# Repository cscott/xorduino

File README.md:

This is an Open Hardware peripheral for the OLPC XO-1/1.5/1.75/4.

The files are created using Eagle 6.2.0 on Linux and the SparkFun footprint
libraries.

Strong inspiration drawn from the following Open Hardware designs (thanks for
sharing!):
* The Arduino Leonardo (arduino-compatible ATmega32U4 design)
* SparkFun's ATmega32U4 breakout <http://www.sparkfun.com/products/11117>
  for figuring out which parts of the Leonardo design are actually
  mandatory
* SparkFun's Scratch Sensor Board-compatible PicoBoard
    <http://www.sparkfun.com/products/10311>

Some notes:

0. This board integrates Arduino, Scratch Sensor Board, and turtle robot
   functionality.  There are many optional parts: if you want to build
   just the Arduino, you may; if you want to populate the robot functionality
   but not the sensor board, that's fine, too.  If you populate the
   peripherals but not the ATmega32u4 processor, this makes a splendid
   "shield" for the XO Stick -- one way to amortize the cost of
   the robot functionality is to have just one XOrduino-bot shield per
   classroom, while still giving the kids their own XO Stick "brains"
   which they can mount on top of it.

    The "bot" features of the board include a current-limited motor driver,
   two bump switches at the front of the board, and two optical sensors
   for measuring motor rotation, allowing the user to write code like
   "rotate left 90 degrees" instead of "rotate left 2 seconds", which
   experimentally kids find much harder to understand.  The XOrduino
   board mounts on a Tamiya Twin Motor Gearbox (part #70097), and there's
   a mounting hole for a ~25mm long standoff to serve as a front skid.

    The motors are set up to draw 1A max, which matches the power source
   ability of the XO's USB ports.  The USB standard only allows 500mA
   draw, which would require adjusting F1 and RN7.

1. Many of the Leonardo design's components are optional in a
   lowest-possible-cost design, for a number of different reasons:
   a) USB port protection which is already included on the XO
      motherboard,
   b) ESD and protection diodes (helpful but not required),
   c) bypass caps and ferrites for less noise on analog signals
      (helpful but not required).
   Wherever possible I've included the pads anyway, so that less
   budget-conscious users can populate these components.  At times
   this has required jumper traces which you need to cut if you
   decide to populate the optional components.

2. I eliminated the multi-way 3.3V/5V internal/external power supply
   functionality of the Arduino to save cost.  The XOrduino is 5V
   only, powered by the USB port.  The Arduino "3.3V" pin on the
   shield connector is left disconnected.  I've replaced this with
   a lower cost step-up regulator, allowing "bot" users to power
   the XOrduino with a 3-cell (4.5v) battery pack.  Again, all
   these components are optional: the XOrduino will run fine
   powered by its USB tether.

3. The first version of this board used a large number of through-hole
   parts.  This revision is less afraid of surface mount parts (since
   the ATmega32U4 is only available in an SMT package anyway), which
   save board space and lower BOM cost.  I'm attempting to make the
   XOrduino local-assembly-friendly, so I surface mount footprints are
   as large as possible: all discrete components are 0805 or larger.
   Like the XO Stick, this has been routed as a two layer board to
   lower reproduction costs, although if you fabricate with a 4-layer
   board you will get more robust power and ground planes.

    One possibly-controversial change in this version is to use
   surface mount resistor arrays to reduce part count and BOM cost;
   they may turn out to be too small to hand assemble.  We'll see.

4. I made this Scratch Sensor Board compatible.  Even though many of
   the scratch sensors are redudant on the XO (it has a microphone
   already, and the XO-1.75 includes an ambient light sensor), they
   gain new relevance in the "turtle bot" mode -- they make it easy to
   build a standalone robot which is "afraid of light", "stops when
   you clap", etc.  The scratch community has a large number of
   interesting examples based around the Scratch Sensor
   Board/Picoboard, many of which can use the 4 additional channels
   provided by the XOrduino ("color etch-a-sketch", for example, with
   knobs for X, Y, color, and line width).  I used 3.5mm jacks instead
   of the Picoboard-standard 2.5mm jacks in order to be compatible
   with probes built for the XO; I hope that was a good choice.

    See https://github.com/osbock/ScratchSensors for an arduino sketch
   to support the Scratch Sensor board functionality; it might be nicer
   to integrate this into the bootloader so that it's "always there".

5. There's a USB plug integrated with the PCB with break-off tabs to
   increase the thickness to the USB standard 1.6mm.  There are pads
   for a through-hole USB mini-B connector and a more-standard surface
   mount USB micro-B connector, but they are rather expensive (~$1).

    When the discrete connector is populated, it leaves the USB
   signals and power/gnd exposed on big metal tabs, which could be
   non-ideal.  Certainly you shouldn't plug in to more than one jack
   at a time.

  -- C. Scott Ananian, 2012-06-09, revised 2012-07-30, 2012-08-08.

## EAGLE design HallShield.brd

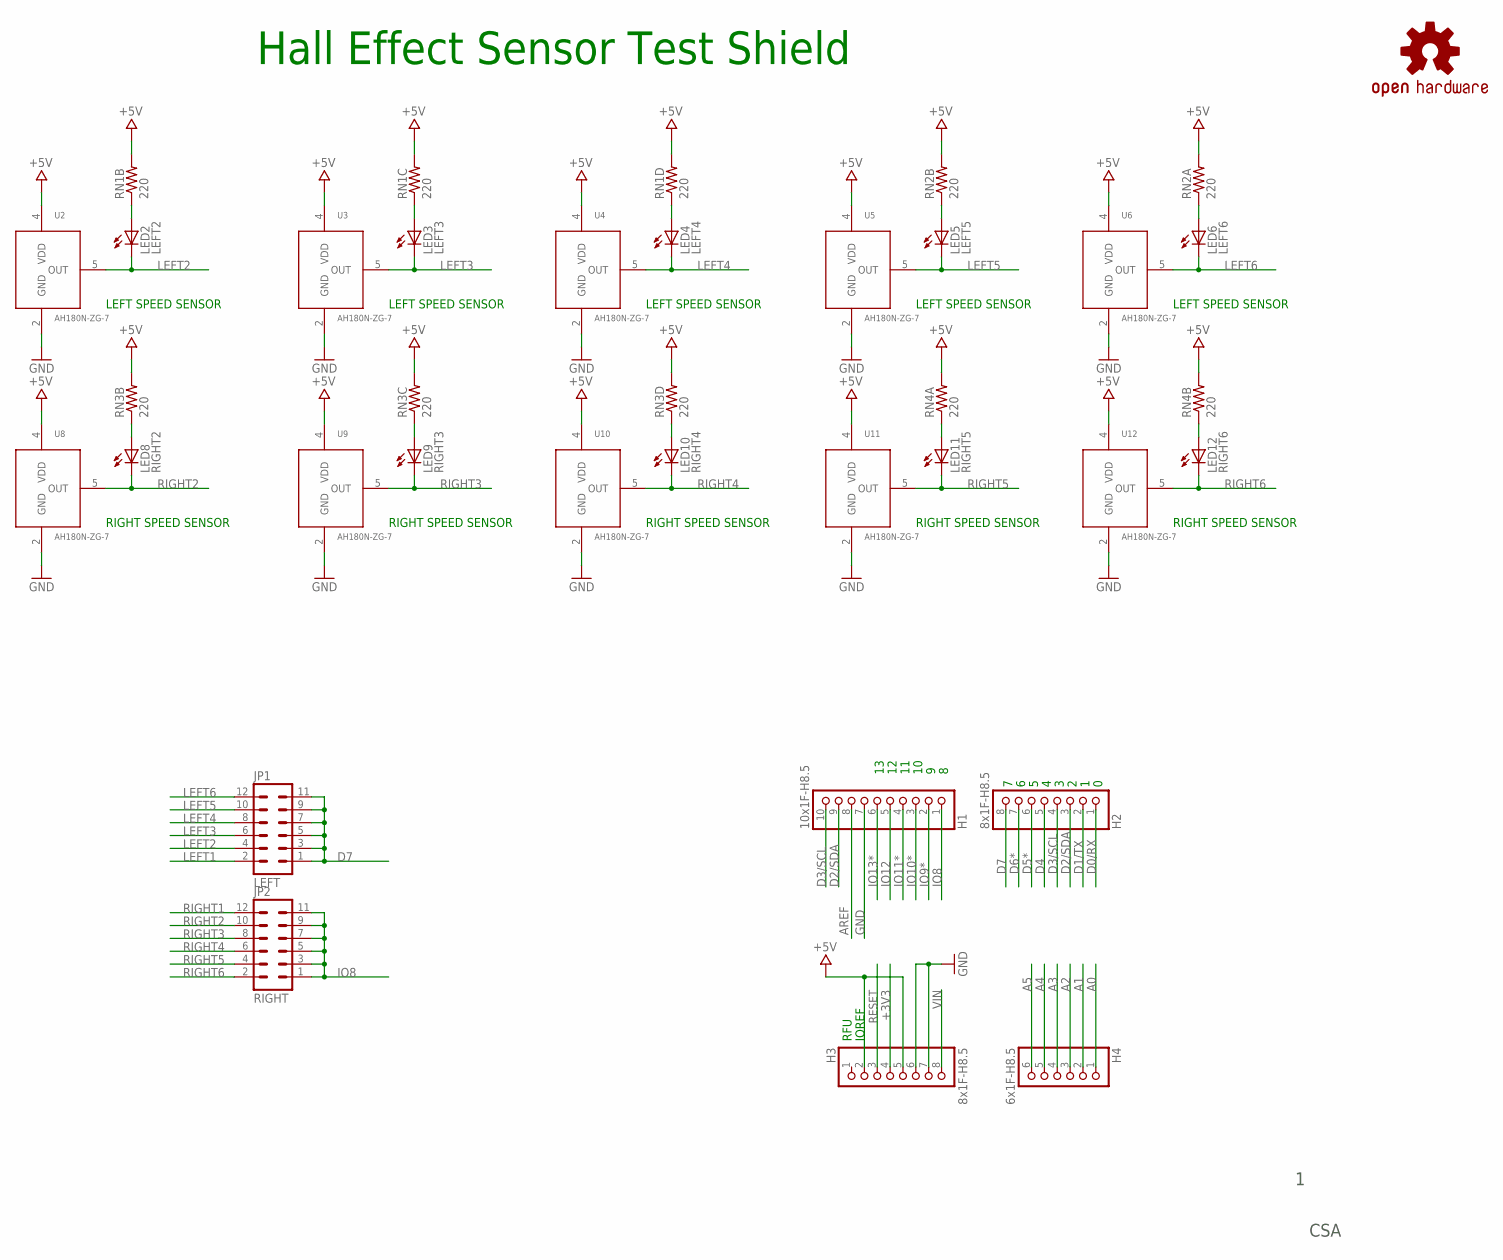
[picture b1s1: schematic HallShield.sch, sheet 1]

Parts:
H1: 10x1F-H8.5; 1X10
H2, H3: 8x1F-H8.5; 1X08
H4: 6x1F-H8.5; 1X06
JP1: LEFT; MA06-2
JP2: RIGHT; MA06-2
LED2: LEFT2; LED0805
LED3: LEFT3; LED0805
LED4: LEFT4; LED0805
LED5: LEFT5; LED0805
LED6: LEFT6; LED0805
LED8: RIGHT2; LED0805
LED9: RIGHT3; LED0805
LED10: RIGHT4; LED0805
LED11: RIGHT5; LED0805
LED12: RIGHT6; LED0805
RN1, RN2, RN3, RN4: 220; CRA06S
U2, U3, U4, U5, U6, U8, U9, U10, U11, U12: AH180N-ZG-7; SOT553
U$5: OSHW-LOGOL; OSHW-LOGO-L

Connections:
+3V3: H3.4
+5V: H3.2, H3.5, RN1.5 (2), RN1.6 (2), RN1.7 (2), RN2.7 (2), RN2.8 (2), RN3.5 (2), RN3.6 (2), RN3.7 (2), RN4.7 (2), RN4.8 (2), U2.4 (VDD), U3.4 (VDD), U4.4 (VDD), U5.4 (VDD), U6.4 (VDD), U8.4 (VDD), U9.4 (VDD), U10.4 (VDD), U11.4 (VDD), U12.4 (VDD); also elsewhere on the board
A0: H4.1
A1: H4.2
A2: H4.3
A3: H4.4
A4: H4.5
A5: H4.6
AREF: H1.8
D0/RX: H2.1
D1/TX: H2.2
D2/SDA: H1.9, H2.3
D3/SCL: H1.10, H2.4
D4: H2.5
D5*: H2.6
D6*: H2.7
D7: H2.8, JP1.1, JP1.3, JP1.5, JP1.7, JP1.9, JP1.11
GND: H1.7, H3.6, H3.7, U2.2 (GND), U3.2 (GND), U4.2 (GND), U5.2 (GND), U6.2 (GND), U8.2 (GND), U9.2 (GND), U10.2 (GND), U11.2 (GND), U12.2 (GND); also elsewhere on the board
IO8: H1.1, JP2.1, JP2.3, JP2.5, JP2.7, JP2.9, JP2.11
IO9*: H1.2
IO10*: H1.3
IO11*: H1.4
IO12: H1.5
IO13*: H1.6
LEFT1: JP1.2; also elsewhere on the board
LEFT2: JP1.4, LED2.C, U2.5 (OUT)
LEFT3: JP1.6, LED3.C, U3.5 (OUT)
LEFT4: JP1.8, LED4.C, U4.5 (OUT)
LEFT5: JP1.10, LED5.C, U5.5 (OUT)
LEFT6: JP1.12, LED6.C, U6.5 (OUT)
unnamed: LED2.A, RN1.2 (1)
unnamed: LED3.A, RN1.3 (1)
unnamed: LED4.A, RN1.4 (1)
unnamed: LED5.A, RN2.2 (1)
unnamed: LED6.A, RN2.1
unnamed: LED8.A, RN3.2 (1)
unnamed: LED9.A, RN3.3 (1)
unnamed: LED10.A, RN3.4 (1)
unnamed: LED11.A, RN4.1
unnamed: LED12.A, RN4.2 (1)
RESET: H3.3
RIGHT1: JP2.12; also elsewhere on the board
RIGHT2: JP2.10, LED8.C, U8.5 (OUT)
RIGHT3: JP2.8, LED9.C, U9.5 (OUT)
RIGHT4: JP2.6, LED10.C, U10.5 (OUT)
RIGHT5: JP2.4, LED11.C, U11.5 (OUT)
RIGHT6: JP2.2, LED12.C, U12.5 (OUT)
VIN: H3.8

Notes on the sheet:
Hall Effect Sensor Test Shield
IOREF
RFU
CSA
LEFT SPEED SENSOR
RIGHT SPEED SENSOR

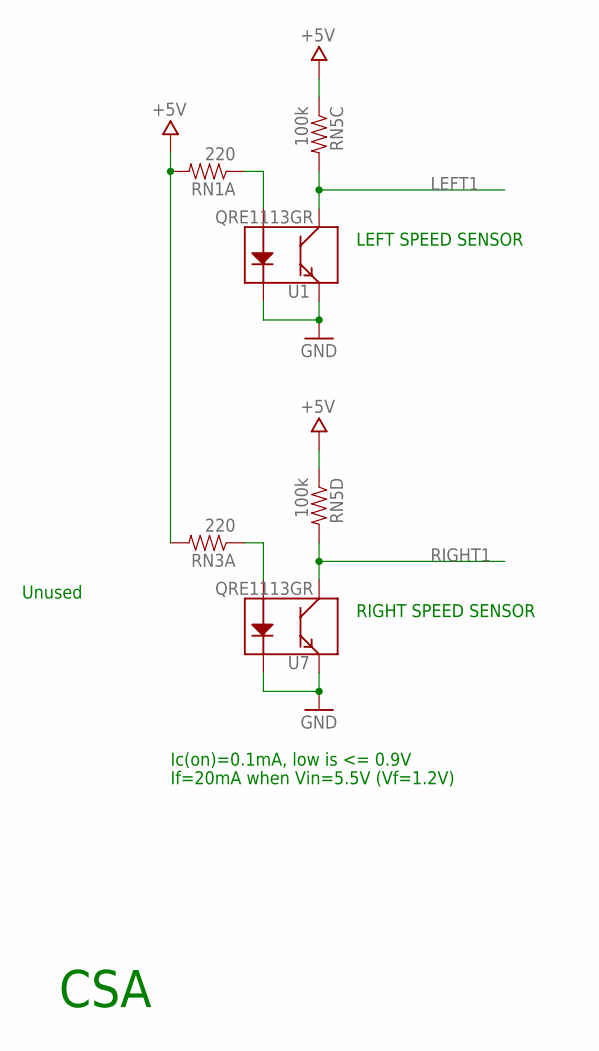
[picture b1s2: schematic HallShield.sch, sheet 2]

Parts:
RN1, RN3: 220; CRA06S
RN5: 100k; CRA06S
U1, U7: QRE1113GR

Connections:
+5V: RN1.8 (2), RN3.8 (2), RN5.3 (1), RN5.4 (1); also elsewhere on the board
GND: U1.2 (K), U1.4 (E), U7.2 (K), U7.4 (E); also elsewhere on the board
LEFT1: RN5.6 (2), U1.3 (C); also elsewhere on the board
RIGHT1: RN5.5 (2), U7.3 (C); also elsewhere on the board
U5_ANODE: RN1.1, U1.1 (A)
U6_ANODE: RN3.1, U7.1 (A)

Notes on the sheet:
LEFT SPEED SENSOR
RIGHT SPEED SENSOR
If=20mA when Vin=5.5V (Vf=1.2V)
Ic(on)=0.1mA, low is <= 0.9V
Unused
CSA

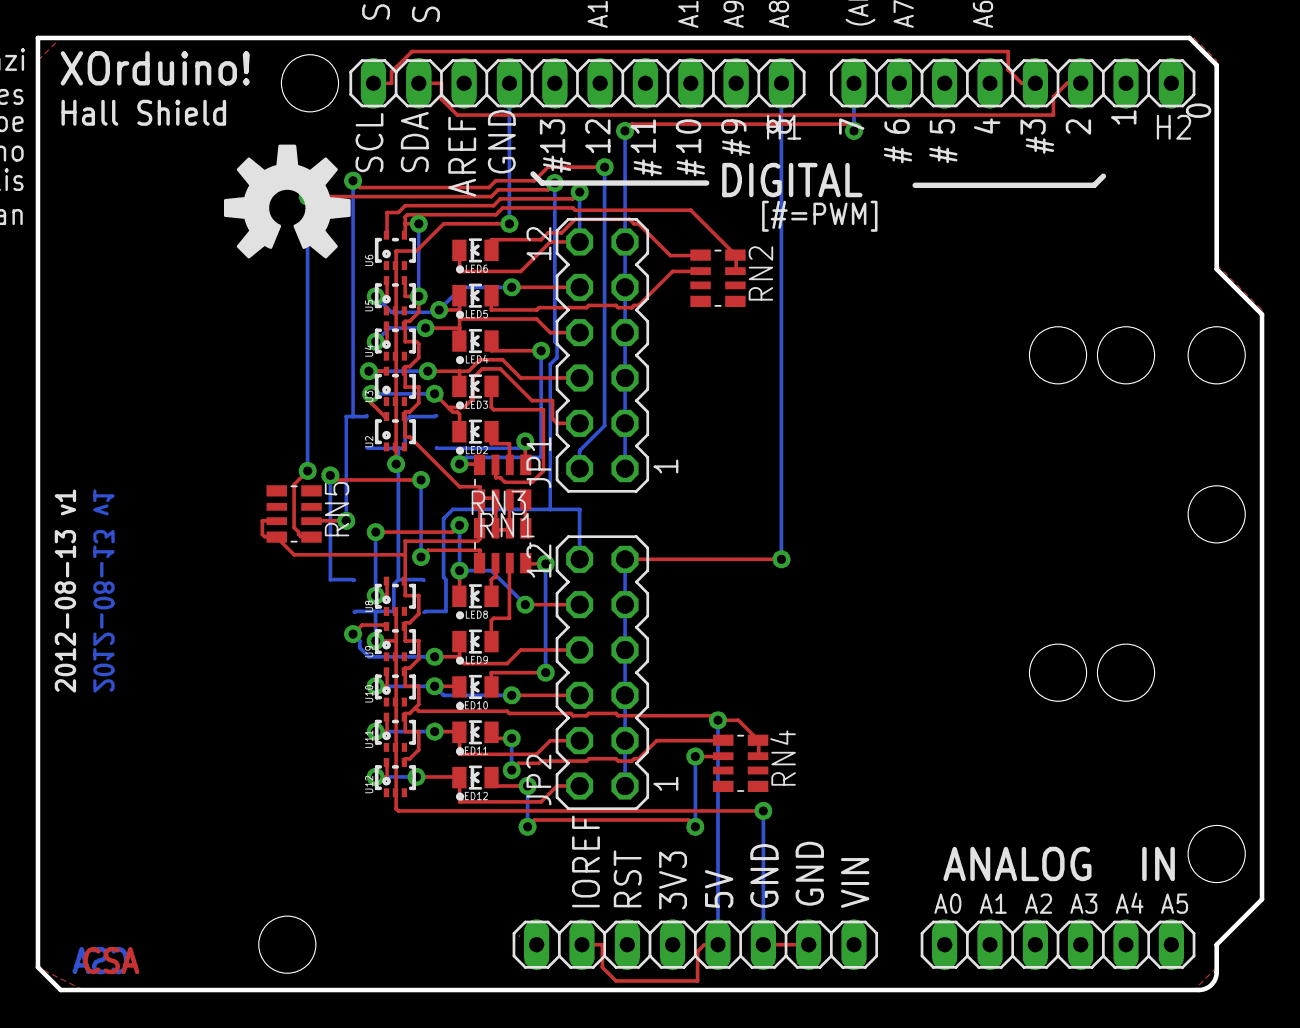
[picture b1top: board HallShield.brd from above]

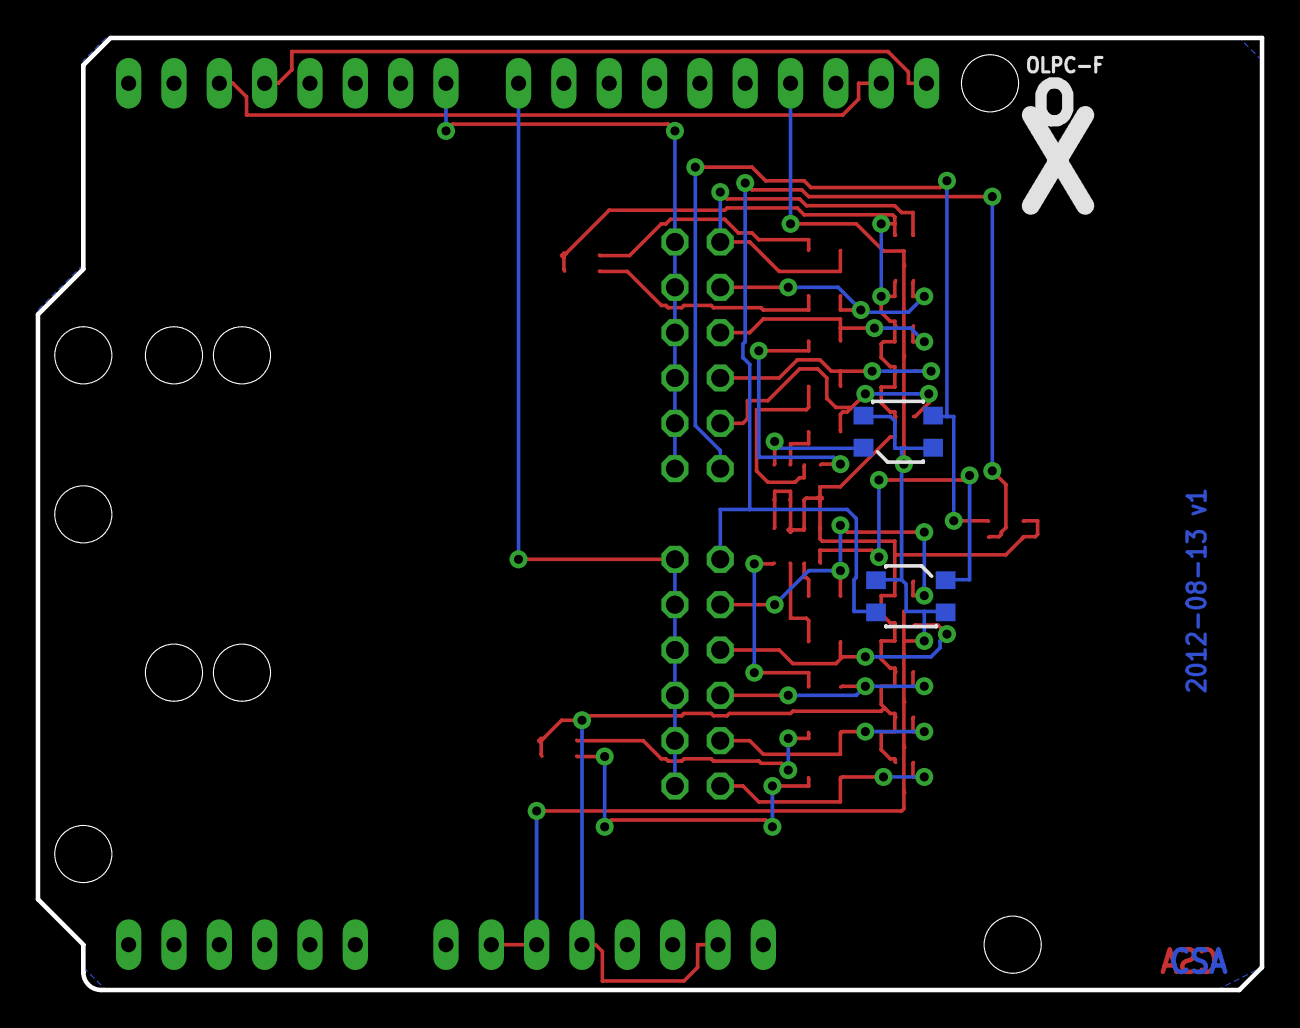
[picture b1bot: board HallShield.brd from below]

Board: 4 copper layers, 68.6 x 53.3 mm, 34 parts (2 on the bottom side), 30 nets.

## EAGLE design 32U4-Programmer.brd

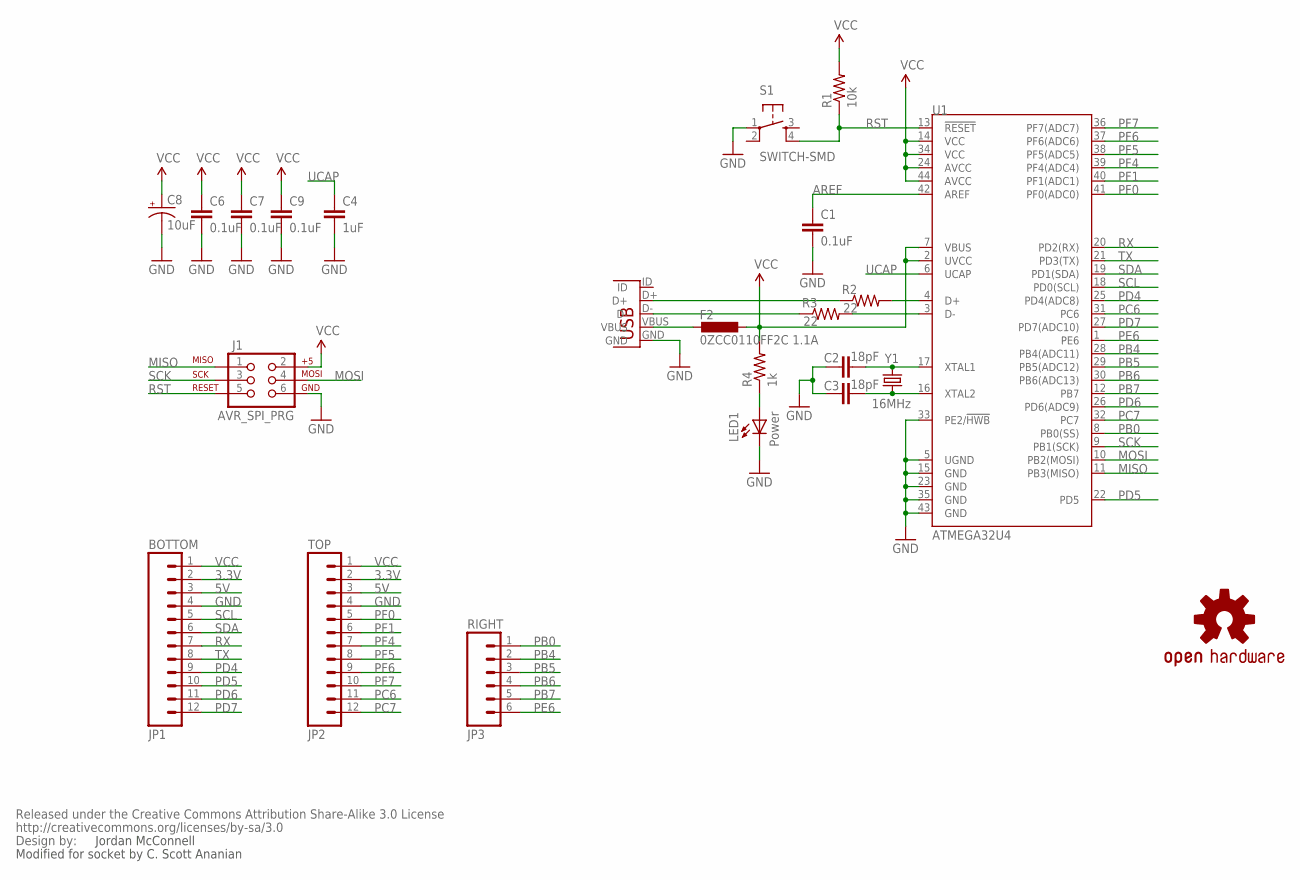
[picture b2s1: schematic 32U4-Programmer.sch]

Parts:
C1, C6, C7, C9: 0.1uF; CAP-PTH-SMALL
C2, C3: 18pF; CAP-PTH-SMALL
C4: 1uF; CAP-PTH-SMALL
C8: 10uF; CPOL-RADIAL-10UF-25V
F2: 0ZCC0110FF2C 1.1A; L1812
J1: AVR_SPI_PRG; 2X3
JP1: BOTTOM; 1X12
JP2: TOP; 1X12
JP3: RIGHT; 1X06
LED1: Power; LED3MM-KIT
R1: 10k; AXIAL-0.3
R2, R3: 22; AXIAL-0.3
R4: 1k; AXIAL-0.3
S1: SWITCH-SMD; TACTILE-PTH
U1: ATMEGA32U4; TQFP44-SOCKET
U$6: OSHW-LOGOM; OSHW-LOGO-M
U$7: CREATIVE_COMMONS
X1: USBMINIB; USB-MB-H2
Y1: 16MHz; HC49US

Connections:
3.3V: JP1.2, JP2.2
5V: JP1.3, JP2.3
AREF: C1.1, U1.42 (AREF)
D_M: R3.P$1 (1), X1.D-
D_P: R2.P$1 (1), X1.D+
GND: C1.2, C2.1, C3.1, C4.2, C6.2, C7.2, C8.2 (-), C9.2, J1.6, JP1.4, JP2.4, LED1.K (C), S1.1, U1.5 (UGND), U1.15 (GND), U1.23 (GND), U1.33 (PE2/!HWB), U1.35 (GND), U1.43 (GND), X1.GND
MISO: J1.1, U1.11 (PB3(MISO))
MOSI: J1.4, U1.10 (PB2(MOSI))
unnamed: F2.2, X1.VBUS
unnamed: C2.2, U1.17 (XTAL1), Y1.2
unnamed: C3.2, U1.16 (XTAL2), Y1.1
unnamed: LED1.A, R4.P$1 (1)
PB0: JP3.1, U1.8 (PB0(SS))
PB4: JP3.2, U1.28 (PB4(ADC11))
PB5: JP3.3, U1.29 (PB5(ADC12))
PB6: JP3.4, U1.30 (PB6(ADC13))
PB7: JP3.5, U1.12 (PB7)
PC6: JP2.11, U1.31 (PC6)
PC7: JP2.12, U1.32 (PC7)
PD4: JP1.9, U1.25 (PD4(ADC8))
PD5: JP1.10, U1.22 (PD5)
PD6: JP1.11, U1.26 (PD6(ADC9))
PD7: JP1.12, U1.27 (PD7(ADC10))
PE6: JP3.6, U1.1 (PE6)
PF0: JP2.5, U1.41 (PF0(ADC0))
PF1: JP2.6, U1.40 (PF1(ADC1))
PF4: JP2.7, U1.39 (PF4(ADC4))
PF5: JP2.8, U1.38 (PF5(ADC5))
PF6: JP2.9, U1.37 (PF6(ADC6))
PF7: JP2.10, U1.36 (PF7(ADC7))
RD_M: R3.P$2 (2), U1.3 (D-)
RD_P: R2.P$2 (2), U1.4 (D+)
RST: J1.5, R1.P$1 (1), S1.4, U1.13 (!RESET)
RX: JP1.7, U1.20 (PD2(RX))
SCK: J1.3, U1.9 (PB1(SCK))
SCL: JP1.5, U1.18 (PD0(SCL))
SDA: JP1.6, U1.19 (PD1(SDA))
TX: JP1.8, U1.21 (PD3(TX))
UCAP: C4.1, U1.6 (UCAP)
VCC: C6.1, C7.1, C8.1 (+), C9.1, F2.1, J1.2, JP1.1, JP2.1, R1.P$2 (2), R4.P$2 (2), U1.2 (UVCC), U1.7 (VBUS), U1.14 (VCC), U1.24 (AVCC), U1.34 (VCC), U1.44 (AVCC)

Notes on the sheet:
Jordan McConnell
Modified for socket by C. Scott Ananian

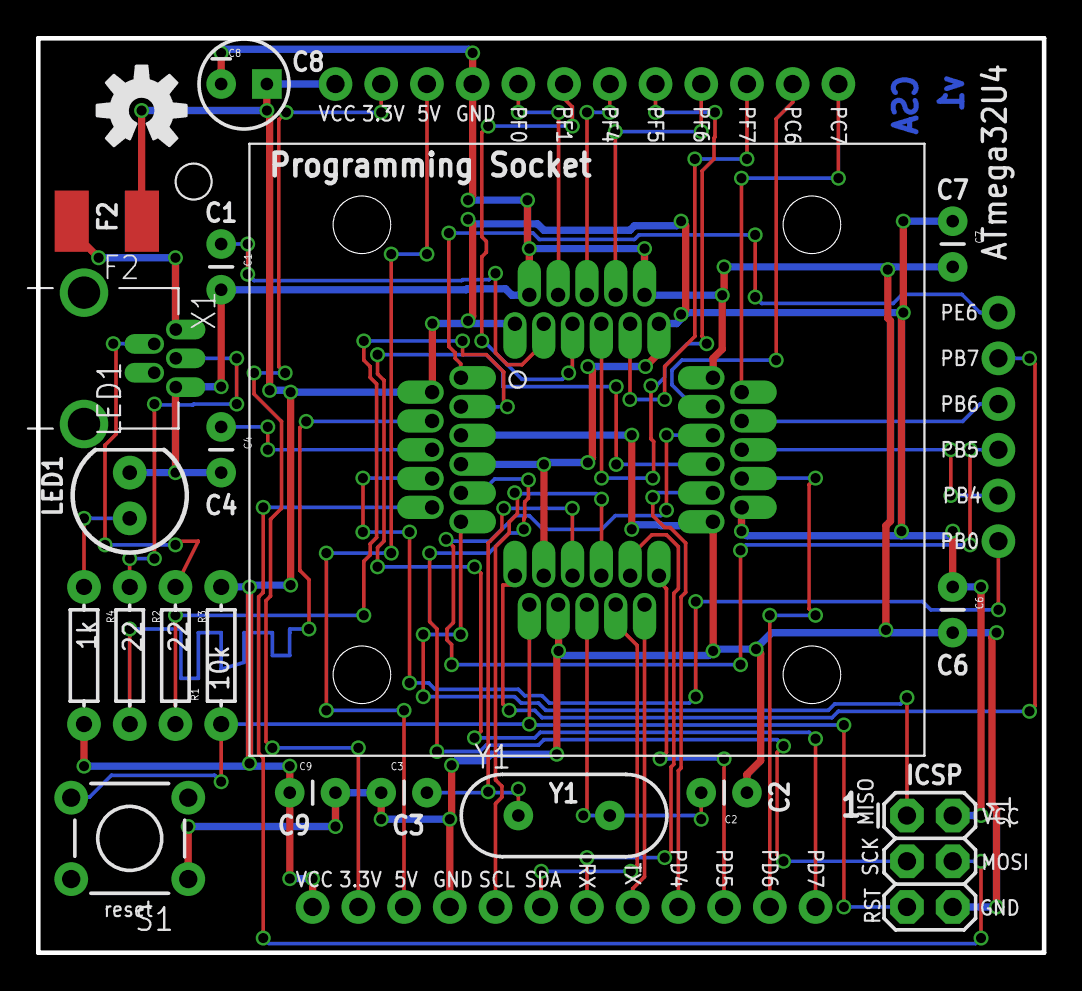
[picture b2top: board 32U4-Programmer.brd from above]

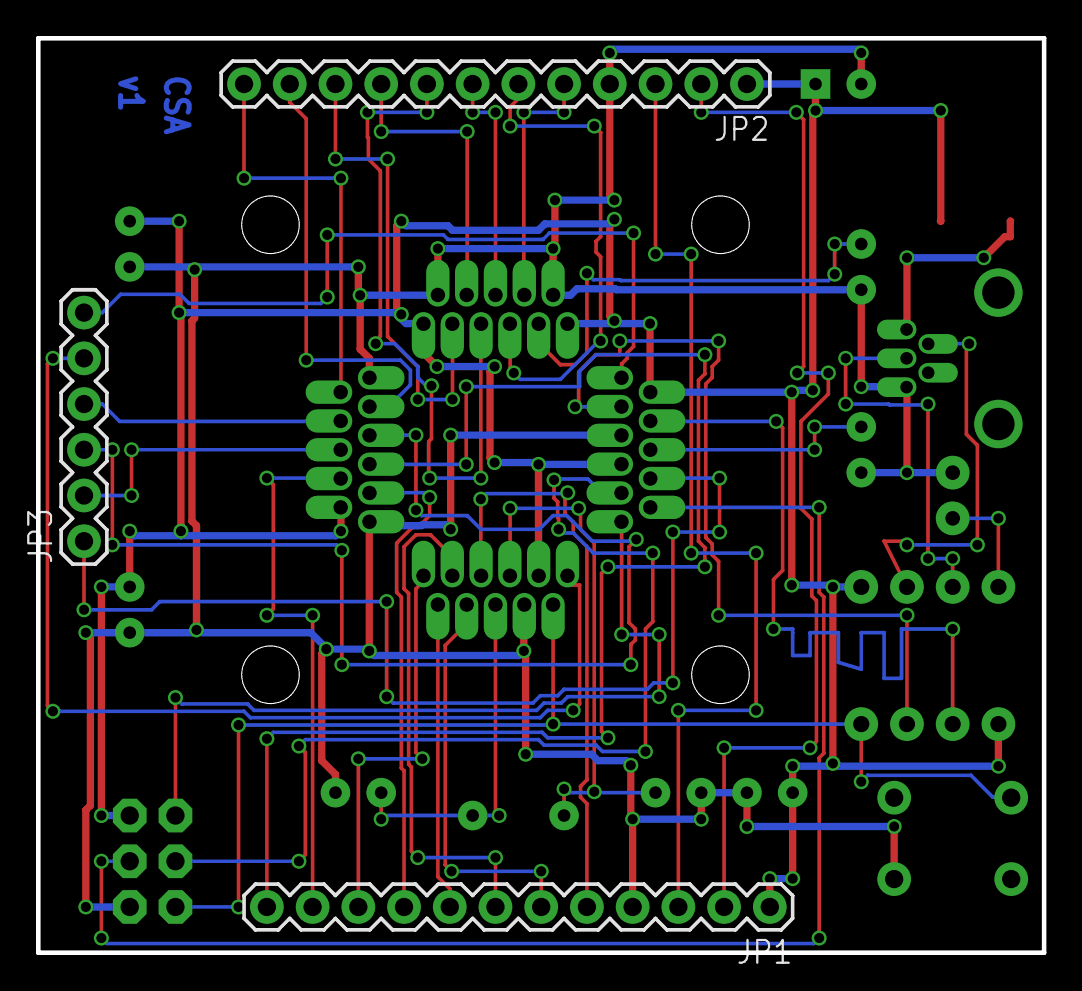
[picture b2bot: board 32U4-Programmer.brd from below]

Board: 2 copper layers, 55.9 x 50.8 mm, 24 parts (3 on the bottom side), 40 nets.

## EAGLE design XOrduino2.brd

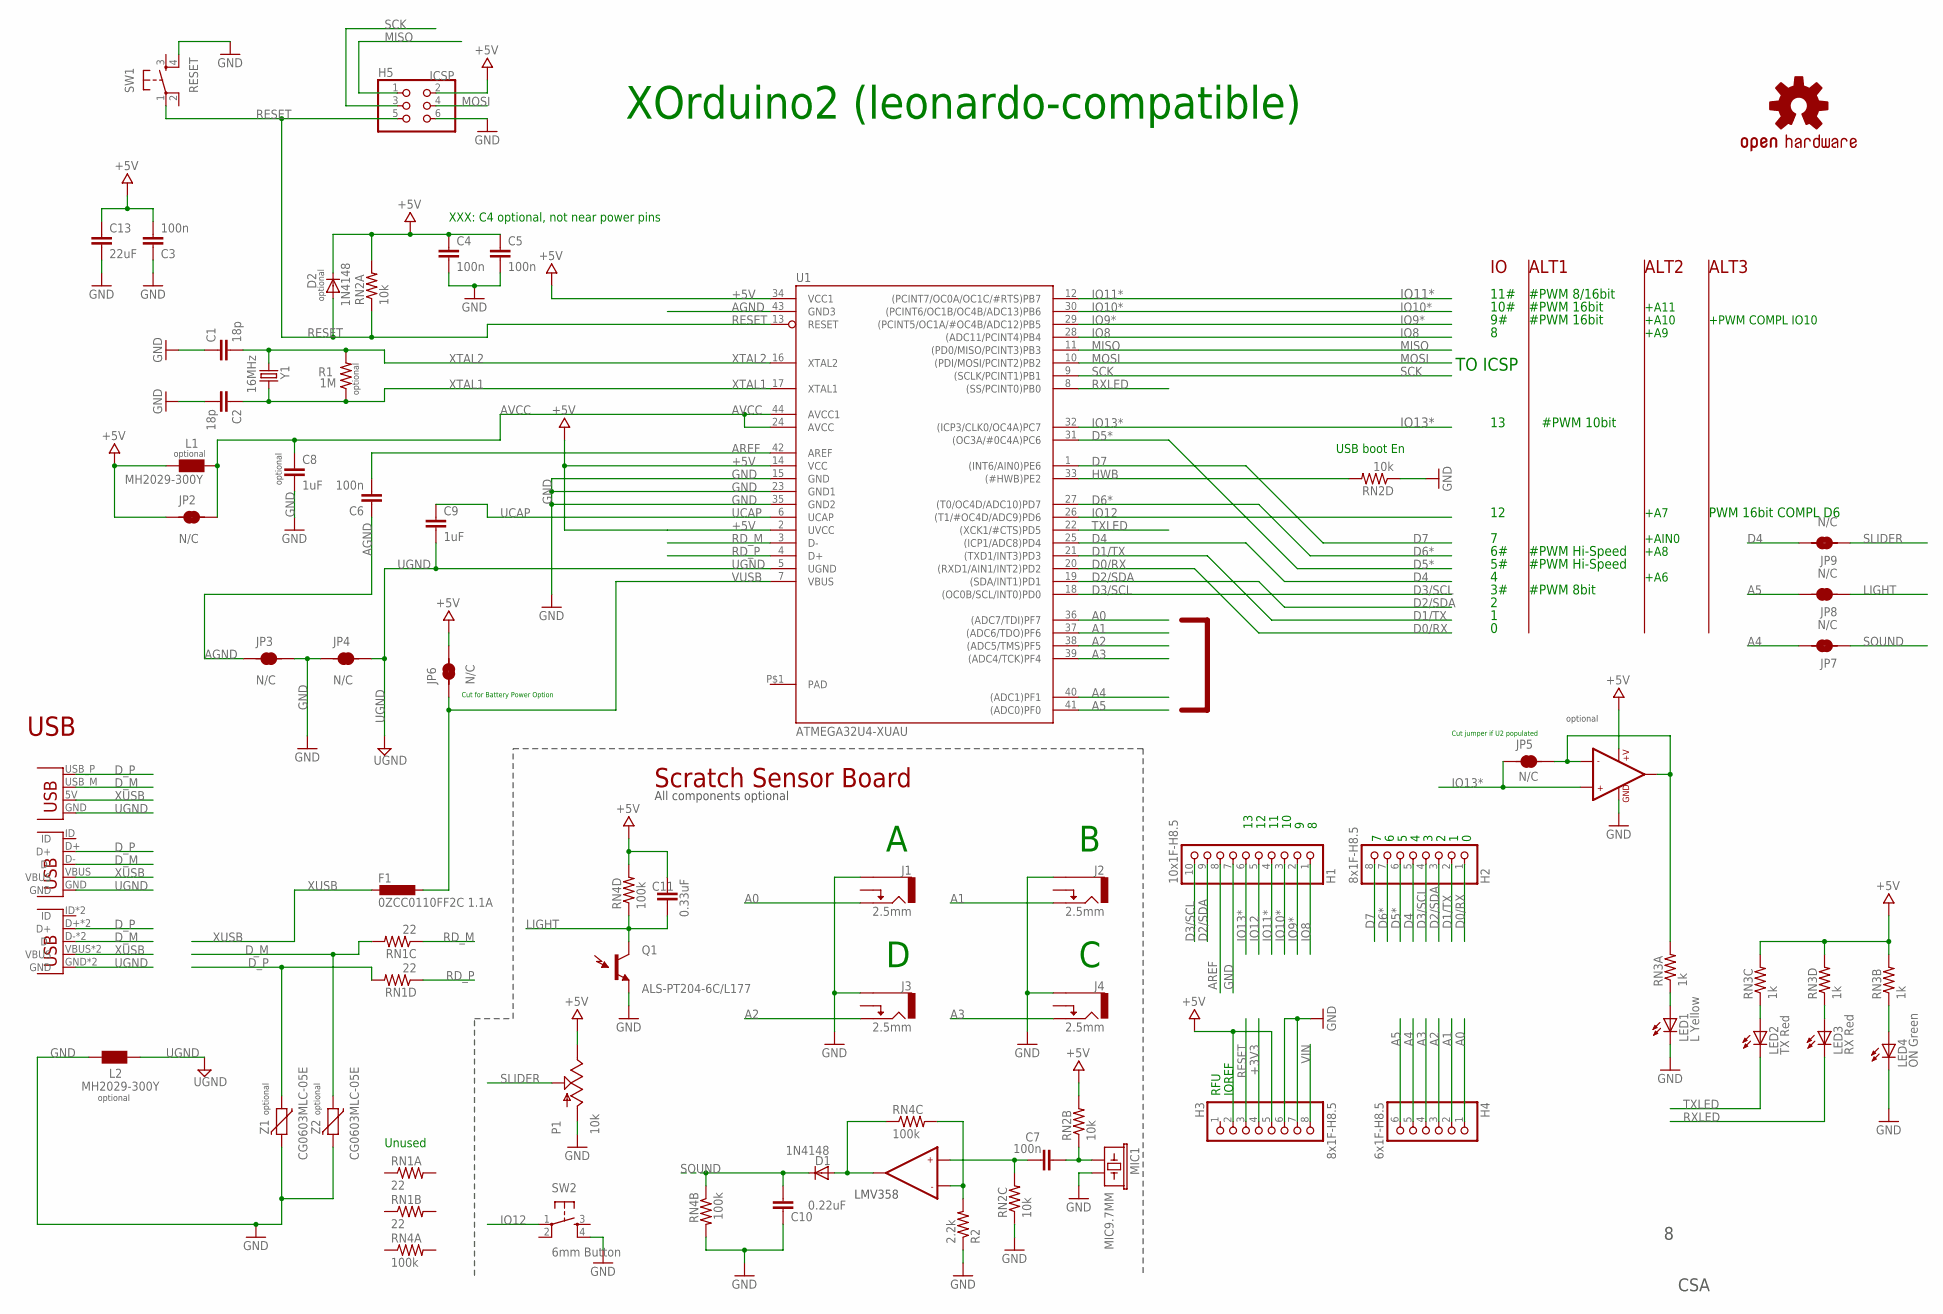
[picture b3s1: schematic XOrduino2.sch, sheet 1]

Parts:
C1, C2: 18p; 0805
C3, C4, C5, C6, C7: 100n; 0805
C8, C9: 1uF; 0805
C10: 0.22uF; 0805
C11: 0.33uF; 0805
C13: 22uF; 1206
D1, D2: 1N4148; DIODE-1N4148
F1: 0ZCC0110FF2C 1.1A; L1812
H1: 10x1F-H8.5; 1X10
H2, H3: 8x1F-H8.5; 1X08
H4: 6x1F-H8.5; 1X06
H5: ICSP; 2X03
J1, J2, J3, J4: 2.5mm; MJ-3523-SMT
JP2, JP3, JP4, JP5, JP6: N/C; SJ-2S-TRACE-NOCONFLICT
JP7, JP8: N/C; SJ-2S-BOT-TRACE-VIA-NOCONFLICT
JP9: N/C; SJ-2S-BOT-TRACE-NOCONFLICT
L1, L2: MH2029-300Y; 0805
LED1: L Yellow; LED0805
LED2: TX Red; LED0805
LED3: RX Red; LED0805
LED4: ON Green; LED0805
MIC1: MIC9.7MM; MIC-9.7MM
P1: 10k; P091N
Q1: ALS-PT204-6C/L177; LED3MM-KIT
R1: 1M; 0805
R2: 2.2k; 0805
RN1: 22; CRA06S
RN2: 10k; CRA06S
RN3: 1k; CRA06S
RN4: 100k; CRA06S
SW1: RESET; TACTILE-PTH
SW2: 6mm Button; TACTILE-PTH
U1: ATMEGA32U4-XUAU; TQFP44-PAD
U2: LMV358; SO08
U$5: OSHW-LOGOL; OSHW-LOGO-L
X1: USBPCB; USB-A-PCB
X2: USBMINIB; USB-MB-H2
X3: USBMICROB-VIA; USB-MICROB-VIA
Y1: 16MHz; HC49US
Z1, Z2: CG0603MLC-05E; CT/CN0603

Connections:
+3V3: H3.4
+5V: C3.2, C4.1, C5.1, C11.1, C13.1, D2.C, H3.2, H3.5, H5.2, JP2.1, JP6.2, L1.1, P1.1 (E), RN2.7 (2), RN2.8 (2), RN3.5 (2), RN3.6 (2), RN3.7 (2), RN4.5 (2), U1.2 (UVCC), U1.14 (VCC), U1.34 (VCC1), U2.8 (+V); also elsewhere on the board
A0: H4.1, J1.2 (TIP), U1.36 ((ADC7/TDI)PF7)
A1: H4.2, J2.2 (TIP), U1.37 ((ADC6/TDO)PF6)
A2: H4.3, J3.2 (TIP), U1.38 ((ADC5/TMS)PF5)
A3: H4.4, J4.2 (TIP), U1.39 ((ADC4/TCK)PF4)
A4: H4.5, JP7.2, U1.40 ((ADC1)PF1)
A5: H4.6, JP8.2, U1.41 ((ADC0)PF0)
AGND: C6.1, JP3.1, U1.43 (GND3)
AREF: C6.2, H1.8, U1.42 (AREF)
AVCC: C8.1, JP2.2, L1.2, U1.24 (AVCC), U1.44 (AVCC1)
D0/RX: H2.1, U1.20 ((RXD1/AIN1/INT2)PD2); also elsewhere on the board
D1/TX: H2.2, U1.21 ((TXD1/INT3)PD3); also elsewhere on the board
D2/SDA: H1.9, H2.3, U1.19 ((SDA/INT1)PD1); also elsewhere on the board
D3/SCL: H1.10, H2.4, U1.18 ((OC0B/SCL/INT0)PD0)
D4: H2.5, JP9.2, U1.25 ((ICP1/ADC8)PD4)
D5*: H2.6, U1.31 ((OC3A/#0C4A)PC6); also elsewhere on the board
D6*: H2.7, U1.27 ((T0/OC4D/ADC10)PD7); also elsewhere on the board
D7: H2.8, U1.1 ((INT6/AIN0)PE6); also elsewhere on the board
D_M: RN1.6 (2), X1.USB_M (D-), X2.D-, X3.D-, X3.D-_VIA (D-), Z2.1
D_P: RN1.5 (2), X1.USB_P (D+), X2.D+, X3.D+, X3.D+_VIA (D+), Z1.1
GND: C1.1, C2.2, C3.1, C4.2, C5.2, C8.2, C10.1, C13.2, H1.7, H3.6, H3.7, H5.6, J1.1 (SLEEVE), J2.1 (SLEEVE), J3.1 (SLEEVE), J4.1 (SLEEVE), JP3.2, JP4.1, L2.2, LED1.C, LED4.C, MIC1.2, P1.3 (A), Q1.A (E1), R2.1, RN2.3 (1), RN2.4 (1), RN4.7 (2), SW1.4, SW2.4, U1.15 (GND), U1.23 (GND1), U1.35 (GND2), U2.4 (GND), Z1.2, Z2.2; also elsewhere on the board
HWB: RN2.5 (2), U1.33 ((#HWB)PE2)
IO8: H1.1, U1.28 ((ADC11/PCINT4)PB4); also elsewhere on the board
IO9*: H1.2, U1.29 ((PCINT5/OC1A/#OC4B/ADC12)PB5); also elsewhere on the board
IO10*: H1.3, U1.30 ((PCINT6/OC1B/OC4B/ADC13)PB6); also elsewhere on the board
IO11*: H1.4, U1.12 ((PCINT7/OC0A/OC1C/#RTS)PB7); also elsewhere on the board
IO12: H1.5, SW2.1, U1.26 ((T1/#OC4D/ADC9)PD6)
IO13*: H1.6, JP5.1, U1.32 ((ICP3/CLK0/OC4A)PC7), U2.3 (+IN1)
IO13_MIRROR: JP5.2, RN3.8 (2), U2.1 (OUT1), U2.2 (-IN1)
LED1_ANODE: LED1.A, RN3.1
LED2_ANODE: LED2.A, RN3.3 (1)
LED3_ANODE: LED3.A, RN3.4 (1)
LED4_ANODE: LED4.A, RN3.2 (1)
LIGHT: C11.2, JP8.1, JP8.VIA6 (1), Q1.K (C1), RN4.4 (1)
MIC_IN: C7.1, MIC1.1, RN2.2 (1)
MISO: H5.1, U1.11 ((PD0/MISO/PCINT3)PB3)
MOSI: H5.4, U1.10 ((PDI/MOSI/PCINT2)PB2)
OPAMP1_M: R2.2, RN4.6 (2), U2.6 (-IN2)
OPAMP1_OUT: D1.A, RN4.3 (1), U2.7 (OUT2)
OPAMP1_P: C7.2, RN2.6 (2), U2.5 (+IN2)
PAD: U1.P$1 (PAD)
RD_M: RN1.3 (1), U1.3 (D-)
RD_P: RN1.4 (1), U1.4 (D+)
RESET: D2.A, H3.3, H5.5, RN2.1, SW1.1, U1.13 (RESET)
RXLED: LED3.C, U1.8 ((SS/PCINT0)PB0)
SCK: H5.3, U1.9 ((SCLK/PCINT1)PB1)
SLIDER: JP9.1, P1.2 (S)
SOUND: C10.2, D1.C, JP7.1, JP7.VIA6 (1), RN4.2 (1)
TXLED: LED2.C, U1.22 ((XCK1/#CTS)PD5)
UCAP: C9.1, U1.6 (UCAP)
UGND: C9.2, JP4.2, L2.1, U1.5 (UGND), X1.GND, X2.GND, X3.GND, X3.GND_VIA (GND)
VIN: H3.8; also elsewhere on the board
VUSB: F1.1, JP6.1, U1.7 (VBUS); also elsewhere on the board
XTAL1: C2.1, R1.1, U1.17 (XTAL1), Y1.2
XTAL2: C1.2, R1.2, U1.16 (XTAL2), Y1.1
XUSB: F1.2, X1.5V (VBUS), X2.VBUS, X3.VBUS, X3.VBUS_VIA (VBUS)

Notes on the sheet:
XOrduino2 (leonardo-compatible)
USB boot En
USB
TO ICSP
10#
11#
#PWM 8bit
#PWM Hi-Speed
#PWM 8/16bit
#PWM 16bit
PWM 16bit COMPL D6
#PWM 10bit
+A6
+A7
IOREF
RFU
+A11
+A10
+A8
+A9
+PWM COMPL IO10
+AIN0
ALT1
ALT2
ALT3
optional
CSA
Scratch Sensor Board
LMV358
All components optional
Cut for Battery Power Option
Cut jumper if U2 populated
Unused
XXX: C4 optional, not near power pins

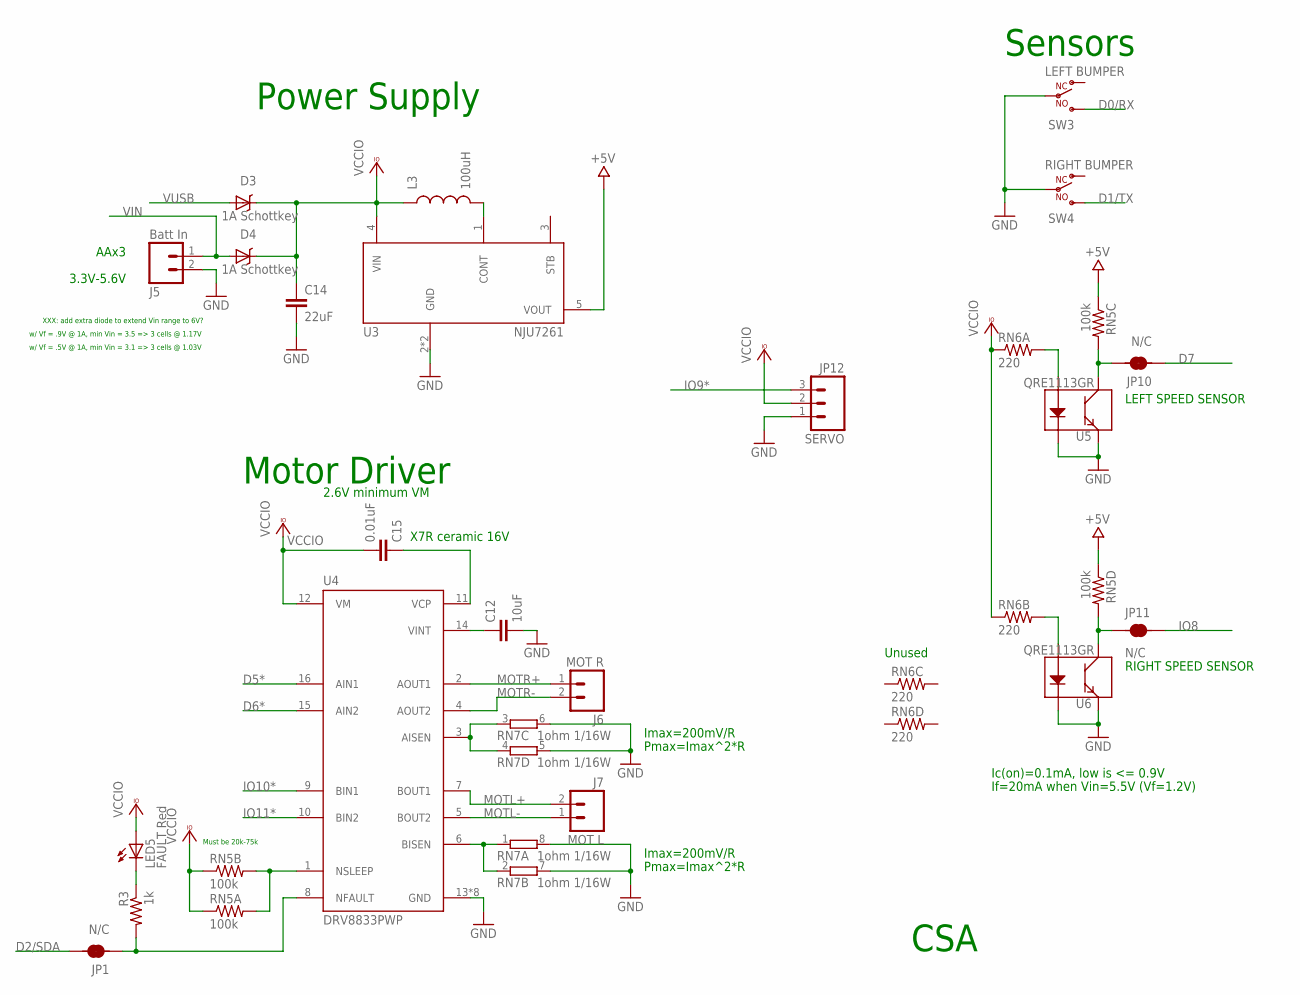
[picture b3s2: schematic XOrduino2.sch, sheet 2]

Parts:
C12: 10uF; 0805
C14: 22uF; 1206
C15: 0.01uF; 0805
D3, D4: 1A Schottkey; SMA-DIODE
J5: Batt In; 1X02
J6: MOT R; SCREWTERMINAL-3.5MM-2
J7: MOT L; SCREWTERMINAL-3.5MM-2
JP1: N/C; SJ-2S-TRACE-NOCONFLICT
JP10, JP11: N/C; SJ-2S-BOT-TRACE-VIA-NOCONFLICT
JP12: SERVO; 1X03
L3: 100uH; 1007
LED5: FAULT Red; LED0805
R3: 1k; 0805
RN5: 100k; CRA06S
RN6: 220; CRA06S
RN7: 1ohm 1/16W; EXB38V
SW3: LEFT BUMPER; SW-LEVER-V1-NOHOLES
SW4: RIGHT BUMPER; SW-LEVER-V2-NOHOLES
U3: NJU7261; SOT89-5
U4: DRV8833PWP; PWP16
U5, U6: QRE1113GR

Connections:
+5V: RN5.3 (1), RN5.4 (1), U3.5 (VOUT); also elsewhere on the board
D0/RX: SW3.NO; also elsewhere on the board
D1/TX: SW4.NO; also elsewhere on the board
D2/SDA: JP1.2; also elsewhere on the board
D5*: U4.16 (AIN1); also elsewhere on the board
D6*: U4.15 (AIN2); also elsewhere on the board
D7: JP10.1, JP10.VIA6 (1); also elsewhere on the board
GND: C12.2, C14.2, J5.2, JP12.1, RN7.5 (2), RN7.6 (2), RN7.7 (2), RN7.8 (2), SW3.C, SW4.C, U3.2 (GND), U3.VIA1 (GND), U4.13 (GND), U4.PPAD (GND), U4.VIA1 (GND), U4.VIA2 (GND), U4.VIA3 (GND), U4.VIA4 (GND), U4.VIA5 (GND), U4.VIA6 (GND), U5.2 (K), U5.4 (E), U6.2 (K), U6.4 (E); also elsewhere on the board
IO8: JP11.2; also elsewhere on the board
IO9*: JP12.3; also elsewhere on the board
IO10*: U4.9 (BIN1); also elsewhere on the board
IO11*: U4.10 (BIN2); also elsewhere on the board
LED5_CATHODE: LED5.C, R3.1
MOTL+: J7.2, U4.7 (BOUT1)
MOTL-: J7.1, U4.5 (BOUT2)
MOTR+: J6.1, U4.2 (AOUT1)
MOTR-: J6.2, U4.4 (AOUT2)
U3_CONT: L3.2, U3.1 (CONT)
U4_AISEN: RN7.3 (1), RN7.4 (1), U4.3 (AISEN)
U4_BISEN: RN7.1, RN7.2 (1), U4.6 (BISEN)
U4_NFAULT: JP1.1, R3.2, U4.8 (NFAULT)
U4_NSLEEP: RN5.7 (2), RN5.8 (2), U4.1 (NSLEEP)
U4_VCP: C15.1, U4.11 (VCP)
U4_VINT: C12.1, U4.14 (VINT)
U5_ANODE: RN6.8 (2), U5.1 (A)
U5_COLLECTOR: JP10.2, RN5.6 (2), U5.3 (C)
U6_ANODE: RN6.7 (2), U6.1 (A)
U6_COLLECTOR: JP11.1, JP11.VIA6 (1), RN5.5 (2), U6.3 (C)
VCCIO: C14.1, C15.2, D3.C, D4.C, JP12.2, L3.1, LED5.A, RN5.1, RN5.2 (1), RN6.1, RN6.2 (1), U3.4 (VIN), U4.12 (VM)
VIN: D4.A, J5.1; also elsewhere on the board
VUSB: D3.A; also elsewhere on the board

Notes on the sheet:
Imax=200mV/R
Pmax=Imax^2*R
LEFT SPEED SENSOR
RIGHT SPEED SENSOR
If=20mA when Vin=5.5V (Vf=1.2V)
Ic(on)=0.1mA, low is <= 0.9V
AAx3
3.3V-5.6V
Motor Driver
Power Supply
Sensors
XXX: add extra diode to extend Vin range to 6V?
2.6V minimum VM
w/ Vf = .9V @ 1A, min Vin = 3.5 => 3 cells @ 1.17V
w/ Vf = .5V @ 1A, min Vin = 3.1 => 3 cells @ 1.03V
X7R ceramic 16V
Unused
Must be 20k-75k
CSA

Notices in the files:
parts and their libraries:
SparkFun: Released under the Creative Commons Attribution Share-Alike 3.0 License
SparkFun: http://creativecommons.org/licenses/by-sa/3.0
SparkFun-Passives: Licensing: CC v3.0 Share-Alike You are welcome to use this library for commercial purposes.
